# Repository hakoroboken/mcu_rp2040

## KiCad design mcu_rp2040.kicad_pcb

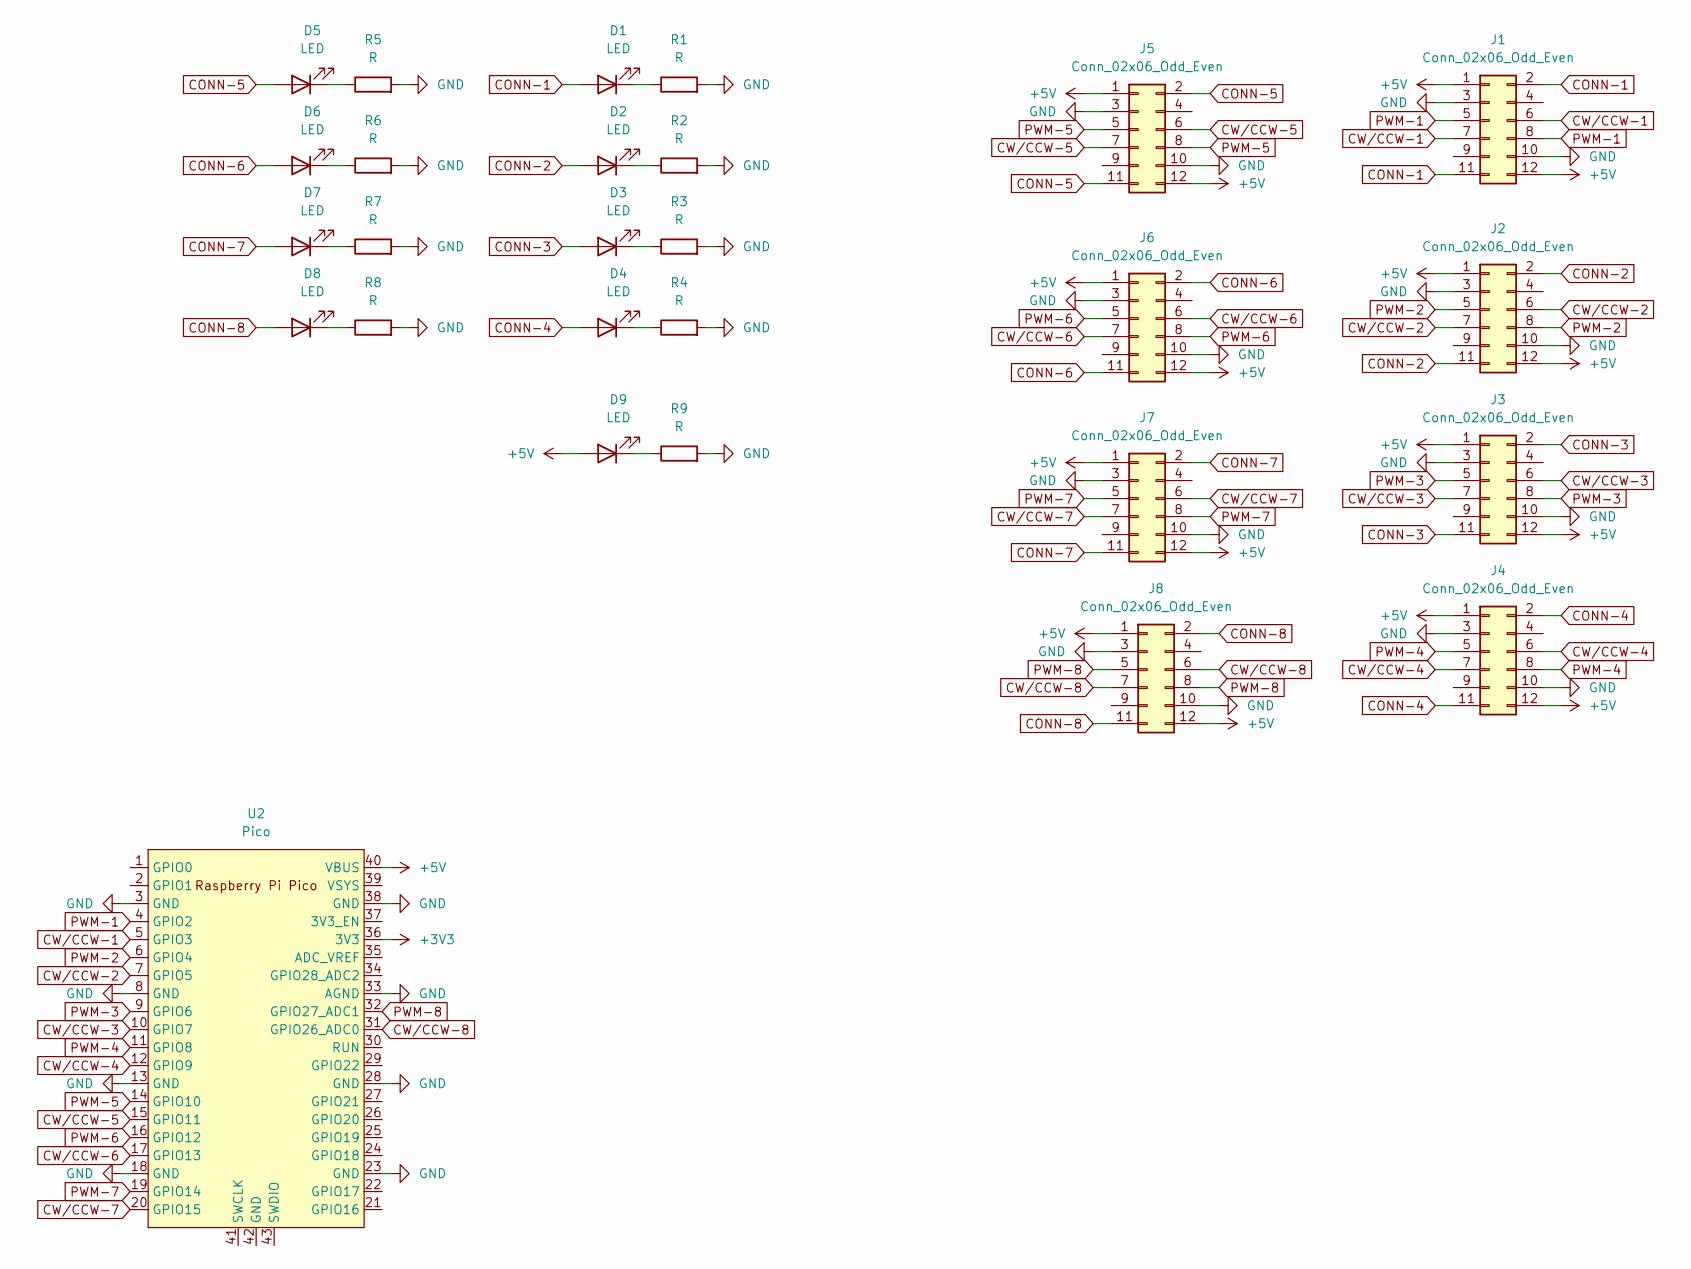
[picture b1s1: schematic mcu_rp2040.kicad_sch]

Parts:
D1, D2, D3, D4, D5, D6, D7, D8, D9: LED; LED_D3.0mm
J1, J2, J3, J4, J5, J6, J7, J8: Conn_02x06_Odd_Even; PinSocket_2x06_P2.54mm_Horizontal
R1, R2, R3, R4, R5, R6, R7, R8, R9: R; R_Axial_DIN0207_L6.3mm_D2.5mm_P10.16mm_Horizontal
U2: Pico; RPi_Pico_SMD_TH

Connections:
+3V3: U2.36 (3V3)
+5V: D9.2 (A), J1.1, J1.12, J2.1, J2.12, J3.1, J3.12, J4.1, J4.12, J5.1, J5.12, J6.1, J6.12, J7.1, J7.12, J8.1, J8.12, U2.40 (VBUS)
CONN-1: D1.2 (A), J1.2, J1.11
CONN-2: D2.2 (A), J2.2, J2.11
CONN-3: D3.2 (A), J3.2, J3.11
CONN-4: D4.2 (A), J4.2, J4.11
CONN-5: D5.2 (A), J5.2, J5.11
CONN-6: D6.2 (A), J6.2, J6.11
CONN-7: D7.2 (A), J7.2, J7.11
CONN-8: D8.2 (A), J8.2, J8.11
CW/CCW-1: J1.6, J1.7, U2.5 (GPIO3)
CW/CCW-2: J2.6, J2.7, U2.7 (GPIO5)
CW/CCW-3: J3.6, J3.7, U2.10 (GPIO7)
CW/CCW-4: J4.6, J4.7, U2.12 (GPIO9)
CW/CCW-5: J5.6, J5.7, U2.15 (GPIO11)
CW/CCW-6: J6.6, J6.7, U2.17 (GPIO13)
CW/CCW-7: J7.6, J7.7, U2.20 (GPIO15)
CW/CCW-8: J8.6, J8.7, U2.31 (GPIO26_ADC0)
GND: J1.3, J1.10, J2.3, J2.10, J3.3, J3.10, J4.3, J4.10, J5.3, J5.10, J6.3, J6.10, J7.3, J7.10, J8.3, J8.10, R1.2, R2.2, R3.2, R4.2, R5.2, R6.2, R7.2, R8.2, R9.2, U2.3 (GND), U2.8 (GND), U2.13 (GND), U2.18 (GND), U2.23 (GND), U2.28 (GND), U2.33 (AGND), U2.38 (GND)
unnamed: D1.1 (K), R1.1
unnamed: D2.1 (K), R2.1
unnamed: D3.1 (K), R3.1
unnamed: D4.1 (K), R4.1
unnamed: D5.1 (K), R5.1
unnamed: D6.1 (K), R6.1
unnamed: D7.1 (K), R7.1
unnamed: D8.1 (K), R8.1
unnamed: D9.1 (K), R9.1
PWM-1: J1.5, J1.8, U2.4 (GPIO2)
PWM-2: J2.5, J2.8, U2.6 (GPIO4)
PWM-3: J3.5, J3.8, U2.9 (GPIO6)
PWM-4: J4.5, J4.8, U2.11 (GPIO8)
PWM-5: J5.5, J5.8, U2.14 (GPIO10)
PWM-6: J6.5, J6.8, U2.16 (GPIO12)
PWM-7: J7.5, J7.8, U2.19 (GPIO14)
PWM-8: J8.5, J8.8, U2.32 (GPIO27_ADC1)

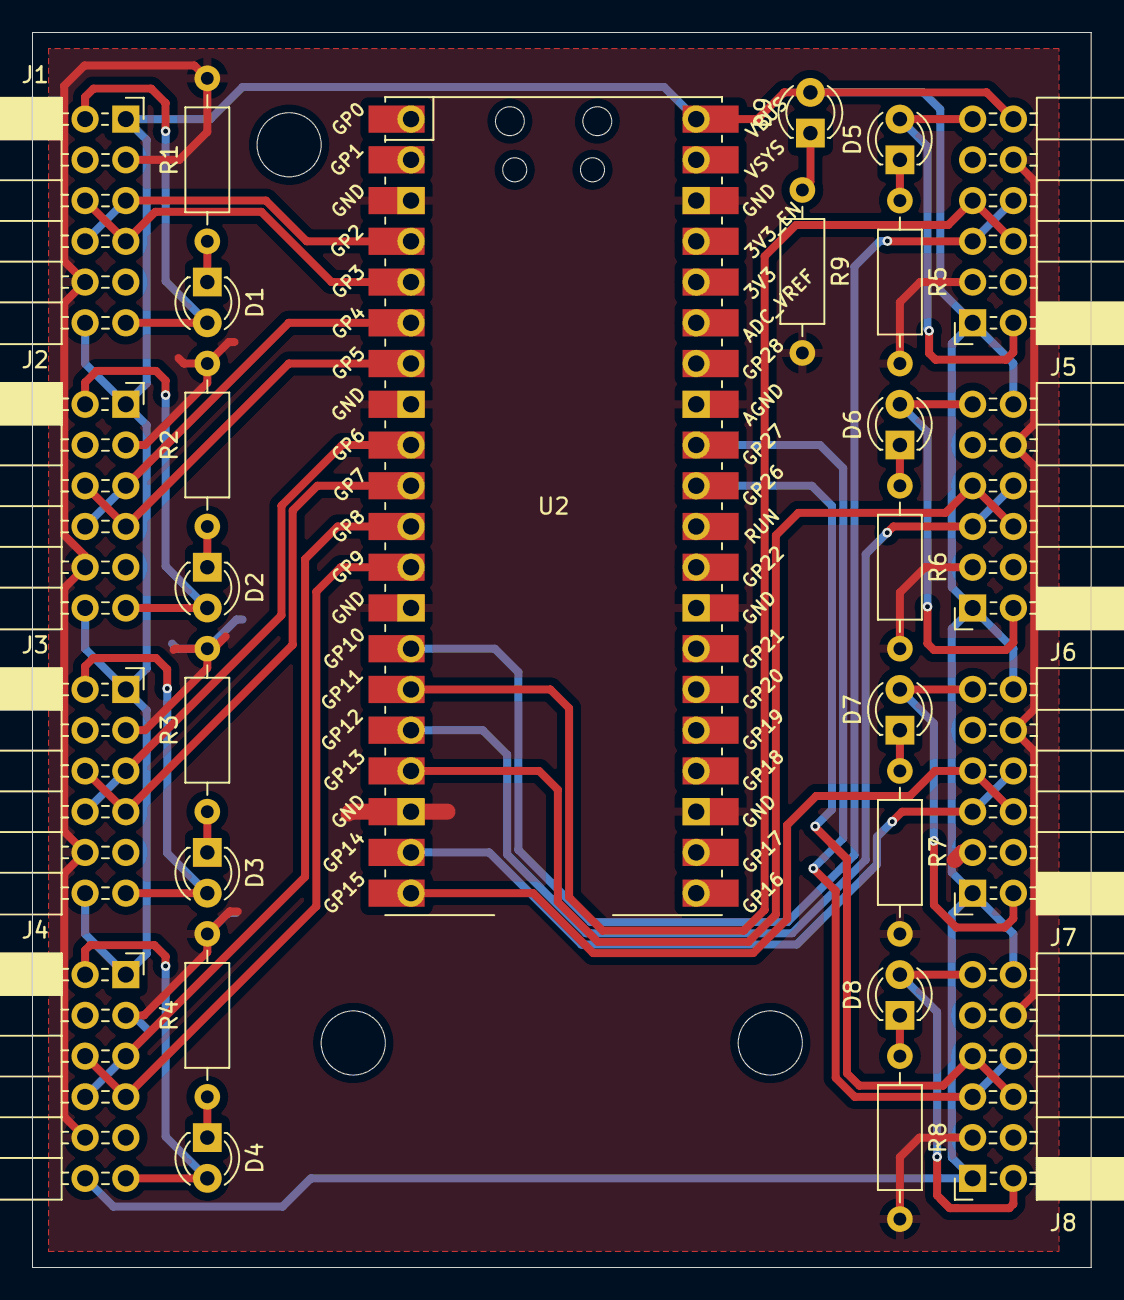
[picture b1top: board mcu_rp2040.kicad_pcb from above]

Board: 2 copper layers, 66.0 x 77.0 mm, 27 parts (0 on the bottom side), 35 nets.

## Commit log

2024-07-03 init
